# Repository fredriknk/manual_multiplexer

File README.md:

# eurocard_mux

 <!-- 3D rendered pretty view -->

10ch -> 10A - 10B mux board for ert measurements. Uses dpdt latching relays to switch between A and B channels. and has front and rear connectors for easy wiring. Allso includes diodes for indicating relay state. 

[PCB layout](./DOCUMENTATION/eurocard_mux_board_prints.pdf) <!-- PDFs of boards -->
[SCHEMATIC](./DOCUMENTATION/eurocard_mux_schematic.pdf) <!-- Schematic PDFs -->

## FRONT

## BACK

## SIDE

# Before major commmits
Remember to run generate_outputs.bat/sh
to update the outputs and pictures.
readmetemplate

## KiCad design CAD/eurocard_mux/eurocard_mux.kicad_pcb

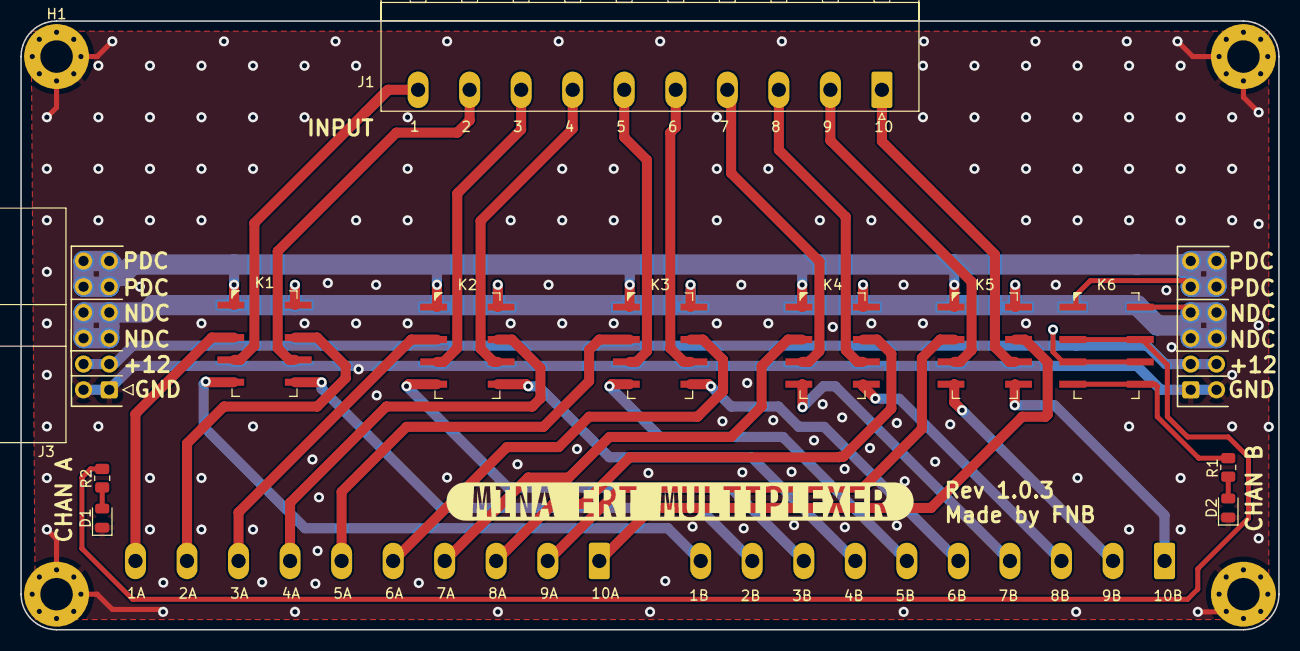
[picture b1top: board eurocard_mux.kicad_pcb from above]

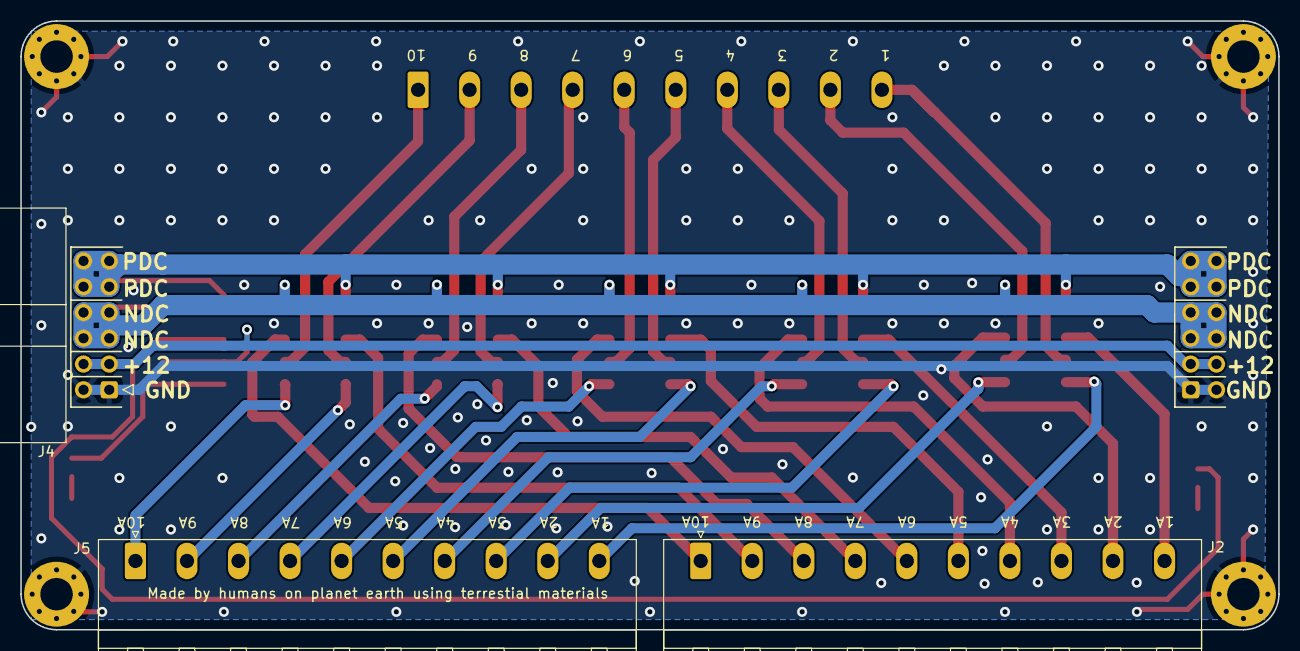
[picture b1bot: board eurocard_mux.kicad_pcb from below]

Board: 2 copper layers, 124.0 x 60.0 mm, 20 parts (3 on the bottom side), 38 nets.

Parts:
D1, D2: LTST-C170KRKT; LED_0805_2012Metric
H1, H2, H3, H4: MountingHole_Pad; MountingHole_3.2mm_M3_Pad_Via
J1, J2, J5: 1759091; PhoenixContact_MSTBA_2,5_10-G-5,08_1x10_P5.08mm_Horizontal
J3, J4: MC-254-12-00-RA-DIP; IDC-Header_2x06_P2.54mm_Horizontal
K1, K2, K3, K4, K5, K6: AGQ210A12Z; Relay_2P2T_10x6mm_TE_IMxxG_Longlegs
R1, R2: 1K1; R_0805_2012Metric
kibuzzard-693809E3: G***; kibuzzard-693809E3

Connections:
+12V: J3.3, J3.4, J4.3, J4.4, K6.3, K6.6
+VDC: J3.9, J3.10, J3.11, J3.12, J4.9, J4.10, J4.11, J4.12, K1.1, K2.1, K3.1, K4.1, K5.1, K6.1
-VDC: J3.5, J3.6, J3.7, J3.8, J4.5, J4.6, J4.7, J4.8, K1.8, K2.8, K3.8, K4.8, K5.8, K6.8
/1: J1.10, K1.3
/1A: J2.10, K1.2
/1B: J5.10, K1.4
/2: J1.9, K1.6
/2A: J2.9, K1.7
/2B: J5.9, K1.5
/3: J1.8, K2.3
/3A: J2.8, K2.2
/3B: J5.8, K2.4
/4: J1.7, K2.6
/4A: J2.7, K2.7
/4B: J5.7, K2.5
/5: J1.6, K3.3
/5A: J2.6, K3.2
/5B: J5.6, K3.4
/6: J1.5, K3.6
/6A: J2.5, K3.7
/6B: J5.5, K3.5
/7: J1.4, K4.3
/7A: J2.4, K4.2
/7B: J5.4, K4.4
/8: J1.3, K4.6
/8A: J2.3, K4.7
/8B: J5.3, K4.5
/9: J1.2, K5.3
/9A: J2.2, K5.2
/9B: J5.2, K5.4
/10: J1.1, K5.6
/10A: J2.1, K5.7
/10B: J5.1, K5.5
/CHNA: K6.2, K6.7, R2.1
/CHNB: K6.4, K6.5, R1.1
GND: D1.1 (K), D2.1 (K), H1.1, H2.1, H3.1, H4.1, J3.1, J3.2, J4.1, J4.2
unnamed: D1.2 (A), R2.2
unnamed: D2.2 (A), R1.2

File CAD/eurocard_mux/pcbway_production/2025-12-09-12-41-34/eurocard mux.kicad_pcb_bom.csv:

Designator,Quantity,Value,Footprint,Package,MPN,DNP,Mount_Type,Description,Sim.Pins,LCSC Part #
"D1, D2",2,LTST-C170KRKT,LED_0805_2012Metric,,,,smt,Light emitting diode,1=K 2=A,
"J1, J2, J5",3,1759091,"PhoenixContact_MSTBA_2,5_10-G-5,08_1x10_P5.08mm_Horizontal",,,,tht,"Generic connector, single row, 01x10, script generated (kicad-library-utils/schlib/autogen/connector/)",,
"J3, J4",2,0901303112,IDC-Header_2x06_P2.54mm_Horizontal,,,,tht,"Generic connector, double row, 02x06, odd/even pin numbering scheme (row 1 odd numbers, row 2 even numbers), script generated (kicad-library-utils/schlib/autogen/connector/)",,
"K1, K2, K3, K4, K5, K6",6,AGQ210A12Z,Relay_2P2T_10x6mm_TE_IMxxG,,,,smt,,,AGQ200S12Z
"R1, R2",2,1K1,R_0805_2012Metric,,,,smt,Resistor,,

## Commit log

2026-01-14 Ran generate outputs
2026-01-14 Fixing readme bug
2026-01-14 Renaming
2026-01-14 Remove " "
2026-01-14 Readme update
2026-01-15 Switched let connections for correct id
